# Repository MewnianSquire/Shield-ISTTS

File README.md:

# Shield ISTTS
 Shield Arduino ISTTS

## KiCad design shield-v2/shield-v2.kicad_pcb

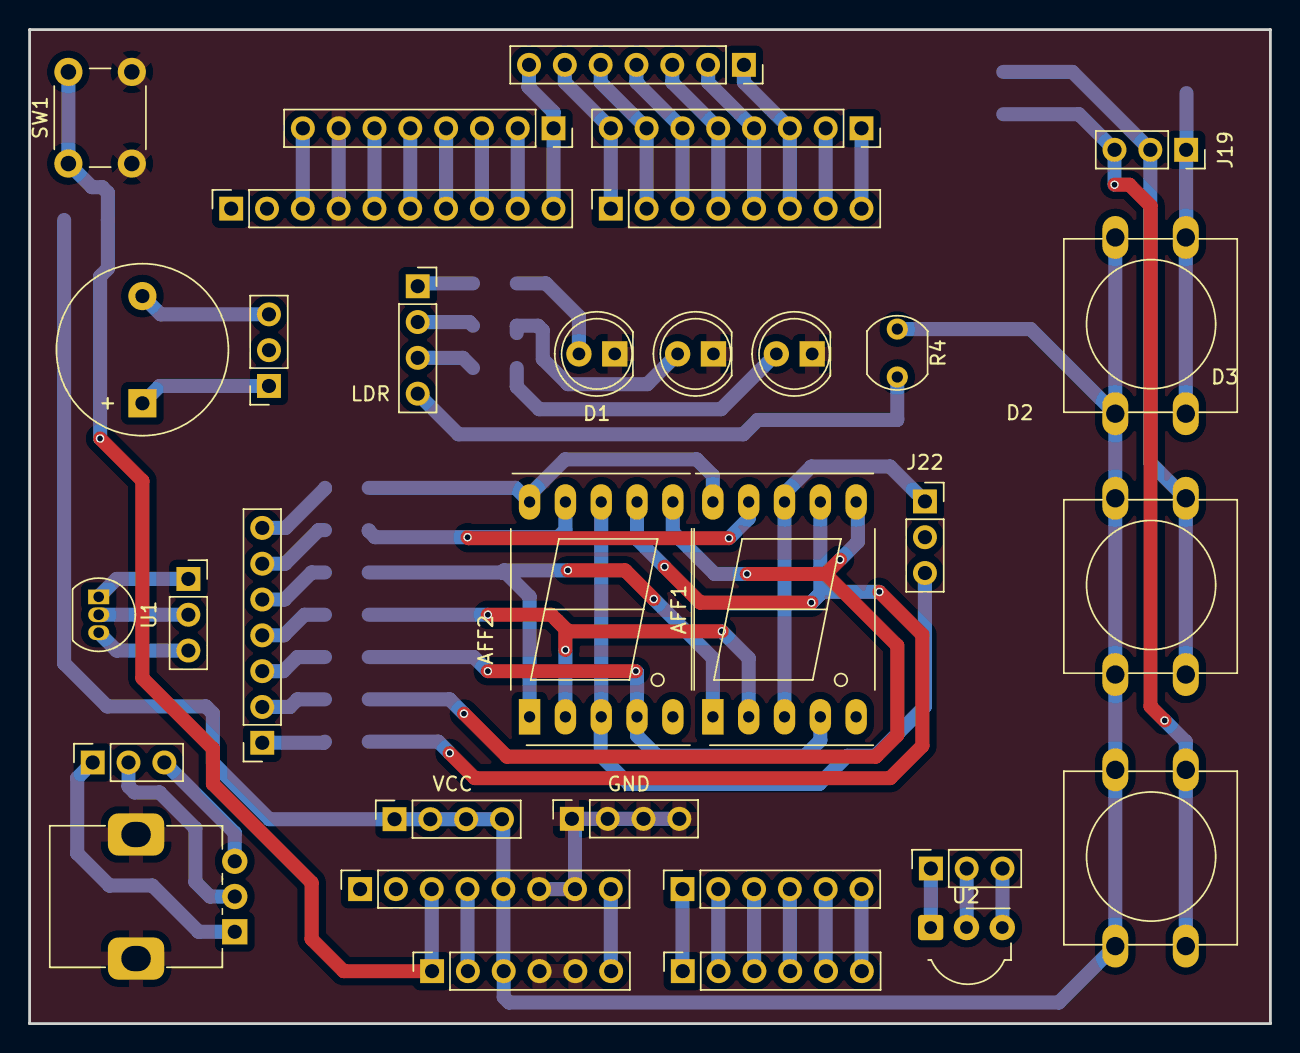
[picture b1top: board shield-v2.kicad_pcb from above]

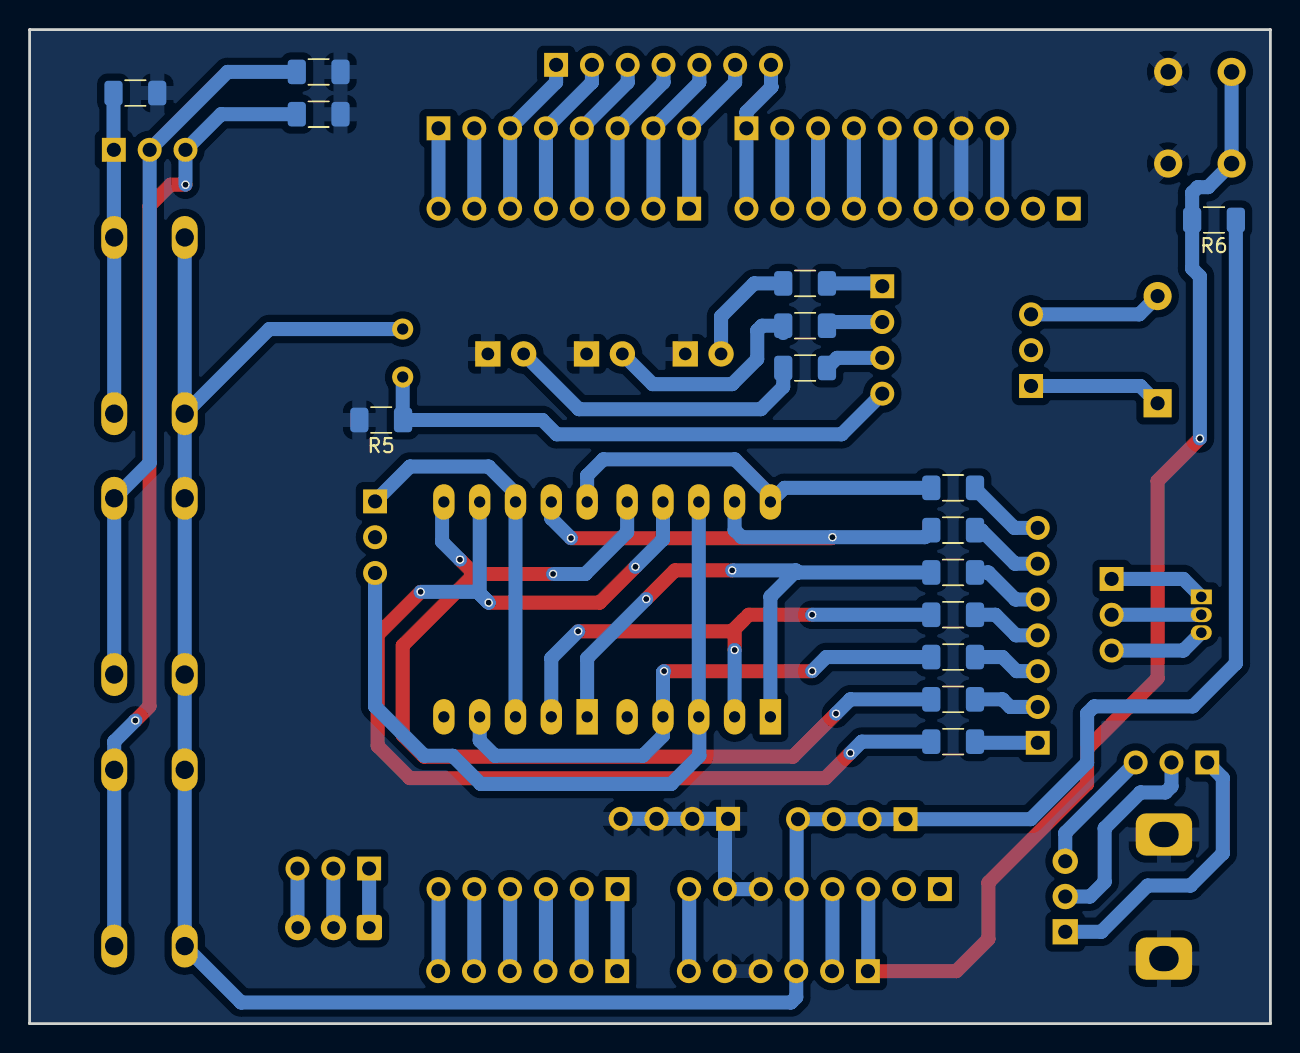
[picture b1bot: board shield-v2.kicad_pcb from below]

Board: 2 copper layers, 88.0 x 70.5 mm, 48 parts (15 on the bottom side), 63 nets.

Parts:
AFF1: D1; 7SegmentLED_LTS6760_LTS6780
AFF2: D2; 7SegmentLED_LTS6760_LTS6780
BZ1: Buzzer; Buzzer_12x9.5RM7.6
D1, D2, D3: LED; LED_D5.0mm
J1: Power; PinSocket_1x08_P2.54mm_Vertical
J2: Digital/PWM; PinSocket_1x10_P2.54mm_Vertical
J3: Analog; PinSocket_1x06_P2.54mm_Vertical
J4: Digital/PWM; PinSocket_1x08_P2.54mm_Vertical
J5: VCC; PinSocket_1x04_P2.54mm_Vertical
J6: GND; PinSocket_1x04_P2.54mm_Vertical
J7: SHIELD POWER; PinSocket_1x06_P2.54mm_Vertical
J8: SHIELD A0-A5; PinSocket_1x06_P2.54mm_Vertical
J9: SHIELD 3-9; PinSocket_1x07_P2.54mm_Vertical
J10: LED+LDR; PinSocket_1x04_P2.54mm_Vertical
J15: BUZZER; PinSocket_1x03_P2.54mm_Vertical
J17: TEMP; PinSocket_1x03_P2.54mm_Vertical
J18: POT; PinSocket_1x03_P2.54mm_Vertical
J19: S1 S2 S3; PinSocket_1x03_P2.54mm_Vertical
J20: 7-SEG; PinSocket_1x07_P2.54mm_Vertical
J21: IR; PinSocket_1x03_P2.54mm_Vertical
J22: D1 D2; PinSocket_1x03_P2.54mm_Vertical
J23: SHIELD 8-15; PinSocket_1x08_P2.54mm_Vertical
J25: SHIELD 0-7; PinSocket_1x08_P2.54mm_Vertical
R1, R2, R3, R5, R10, R11, R12, R13, R14, R15, R16: 330; R_1206_3216Metric_Pad1.30x1.75mm_HandSolder
R4: LDR07; R_LDR_5.1x4.3mm_P3.4mm_Vertical
R6, R7, R8, R9: 10k; R_1206_3216Metric_Pad1.30x1.75mm_HandSolder
RV1: R_Potentiometer_MountingPin; Potentiometer_Alps_RK09K_Single_Vertical
SW1: RESET; SW_PUSH_6mm
SW2: S1; SW_PUSH-12mm
SW3: S2; SW_PUSH-12mm
SW4: S3; SW_PUSH-12mm
U1: LM35-LP; TO-92_Inline
U2: TL1838; Vishay_MOLD-3Pin

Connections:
+3V3: J1.4, J7.2
+5V: J1.5, J5.1, J5.2, J5.3, J5.4, J7.3, R4.1, R6.1, SW2.1, SW3.1, SW4.1
/2: J4.6, J9.1, J25.3
/4: J4.4, J9.3, J25.5
/7: J4.1, J9.6, J25.8
/8: J2.10, J9.7, J23.1
/12: J2.6, J23.5
/13: J2.5, J23.6
/*3: J4.5, J9.2, J25.4
/*5: J4.3, J9.4, J25.6
/*6: J4.2, J9.5, J25.7
/*9: J2.9, J23.2
/*10: J2.8, J23.3
/*11: J2.7, J23.4
/A0: J3.1, J8.1
/A1: J3.2, J8.2
/A2: J3.3, J8.3
/A3: J3.4, J8.4
/AREF: J2.3, J23.8
/RX/0: J4.8, J25.1
/SCL/A5: J3.6, J8.6
/SDA/A4: J3.5, J8.5
/TX/1: J4.7, J25.2
/~RESET: J1.3, J7.1, R6.2, SW1.1
GND: D1.1 (K), D2.1 (K), D3.1 (K), J1.6, J1.7, J2.4, J6.1, J6.2, J6.3, J6.4, J7.4, J7.5, J23.7, R5.2, R7.1, R8.2, R9.2, RV1.MP (MountPin), SW1.2
unnamed: AFF1.7 (a), AFF2.7 (a), R10.1
unnamed: AFF1.6 (b), AFF2.6 (b), R11.1
unnamed: AFF1.4 (c), AFF2.4 (c), R12.1
unnamed: AFF1.2 (d), AFF2.2 (d), R13.1
unnamed: AFF1.1 (e), AFF2.1 (e), R14.1
unnamed: AFF1.9 (f), AFF2.9 (f), R15.1
unnamed: AFF1.10 (g), AFF2.10 (g), R16.1
unnamed: BZ1.2 (+), J15.3
unnamed: BZ1.1 (-), J15.1
unnamed: D1.2 (A), R1.2
unnamed: D2.2 (A), R2.2
unnamed: D3.2 (A), R3.2
unnamed: J10.1, R1.1
unnamed: J10.2, R2.1
unnamed: J10.3, R3.1
unnamed: J10.4, R4.2, R5.1
unnamed: J17.1, U1.1 (+V_{S})
unnamed: J17.2, U1.2 (V_{OUT})
unnamed: J17.3, U1.3 (GND)
unnamed: J18.1, RV1.1
unnamed: J18.2, RV1.2
unnamed: J18.3, RV1.3
unnamed: J19.1, R9.1, SW2.2
unnamed: J19.2, R8.1, SW3.2
unnamed: J19.3, R7.2, SW4.2
unnamed: J20.1, R10.2
unnamed: J20.2, R11.2
unnamed: J20.3, R12.2
unnamed: J20.4, R13.2
unnamed: J20.5, R14.2
unnamed: J20.6, R15.2
unnamed: J20.7, R16.2
unnamed: J21.1, U2.1 (OUT)
unnamed: J21.2, U2.2 (Vs)
unnamed: J21.3, U2.3 (GND)
unnamed: AFF1.3 (C.A.), AFF1.8 (C.A.), J22.1
unnamed: AFF2.3 (C.A.), AFF2.8 (C.A.), J22.3
VCC: J1.8, J7.6

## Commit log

2024-01-26 First Upload
    Contains KiCad project files.
2024-01-26 Second update
    Update 2
